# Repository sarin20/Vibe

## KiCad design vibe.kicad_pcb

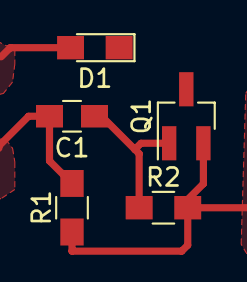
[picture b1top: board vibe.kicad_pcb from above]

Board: 2 copper layers, 5 parts (0 on the bottom side), 4 nets.

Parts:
C1: C; C_0805_HandSoldering
D1: LED; LED_0805_HandSoldering
Q1: Q_NMOS_GSD; SOT-23_Handsoldering
R1, R2: R; R_0805_HandSoldering

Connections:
GND: Q1.2, R1.1, R2.2
IN: C1.2, D1.2, R1.2
unnamed: C1.1, Q1.1, R2.1
OUT: D1.1, Q1.3

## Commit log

2017-12-25 init
